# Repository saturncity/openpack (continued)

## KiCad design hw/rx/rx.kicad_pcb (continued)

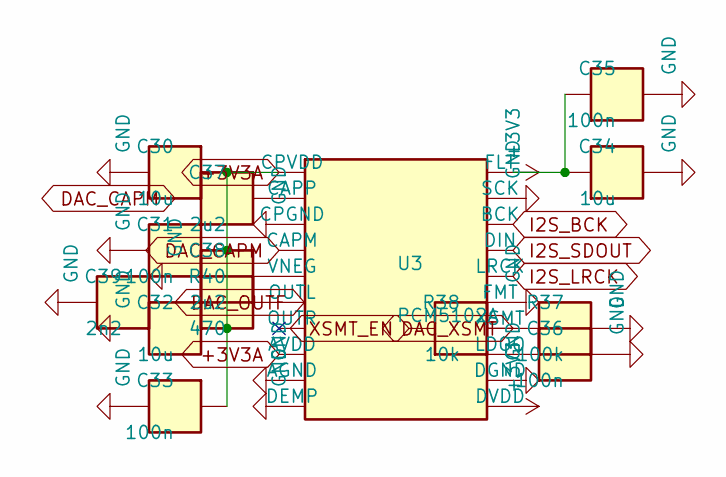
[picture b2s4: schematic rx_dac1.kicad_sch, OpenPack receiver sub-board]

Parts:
C30, C32, C34: 10u; C_0603_1608Metric; MPN C_10u_0603_X5R
C31, C33, C35, C36: 100n; C_0402_1005Metric; MPN C_100n_0402
C37, C38: 2u2; C_0603_1608Metric; MPN C_2u2_0603_X7R
C39: 2n2; C_0402_1005Metric; MPN C_2n2_0402_C0G
R37: 100k; R_0402_1005Metric; MPN R_0402_1%
R38: 10k; R_0402_1005Metric; MPN R_0402_1%
R40: 470; R_0402_1005Metric; MPN R_0402_1%
U3: PCM5102A; TSSOP-20_4.4x6.5mm_P0.65mm; MPN PCM5102APWR

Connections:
+3V3A: C30.1, C31.1, C32.1, C33.1, U3.1 (CPVDD), U3.8 (AVDD); also elsewhere on the board
DAC_CAPM: C37.2, U3.4 (CAPM)
DAC_CAPP: C37.1, U3.2 (CAPP)
DAC_LDOO: C36.1, U3.18 (LDOO)
DAC_OUTF: C39.1, R40.2; also elsewhere on the board
DAC_OUTL: R40.1, U3.6 (OUTL)
DAC_VNEG: C38.1, U3.5 (VNEG)
DAC_XSMT: R37.1, R38.2, U3.17 (XSMT); also elsewhere on the board
I2S_BCK: U3.13 (BCK); also elsewhere on the board
I2S_LRCK: U3.15 (LRCK); also elsewhere on the board
I2S_SDOUT: U3.14 (DIN); also elsewhere on the board
XSMT_EN: R38.1; also elsewhere on the board

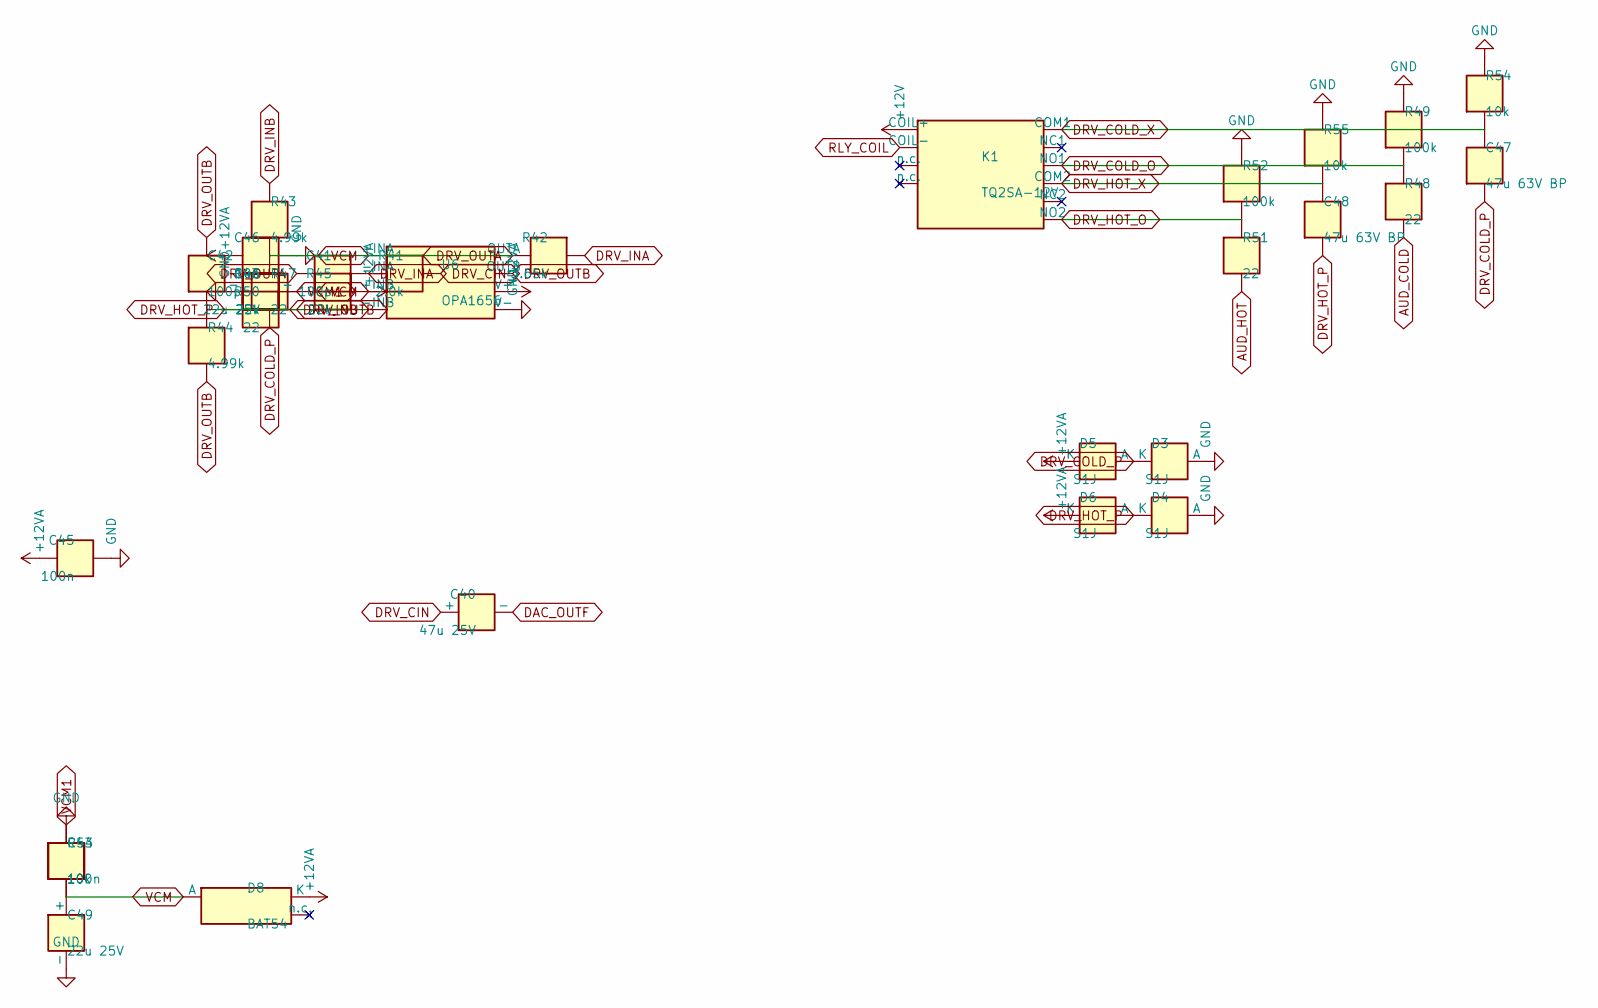
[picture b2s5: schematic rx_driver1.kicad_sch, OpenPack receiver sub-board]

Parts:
C40: 47u 25V; CP_Elec_5x5.4; MPN ALU_47u_25V
C41, C42: 100p; C_0402_1005Metric; MPN C_100p_0402_C0G
C43, C49: 22u 25V; CP_Elec_5x5.4; MPN ALU_22u_25V
C44, C45: 100n; C_0402_1005Metric; MPN C_100n_0402
C46: 10u; C_1206_3216Metric; MPN C_10u_1206_25V_X7R
C47, C48: 47u 63V BP; CP_Radial_D10.0mm_P5.00mm; MPN ALU_BP_47u_63V
D3, D4, D5, D6: S1J; D_SMA; MPN S1J
D8: BAT54; SOT-23; MPN BAT54,215
K1: TQ2SA-12V; Panasonic_TQ2SA; MPN TQ2SA-12V
R41: 2.0k; R_0402_1005Metric; MPN R_0402_1%
R42: 3.65k; R_0402_1005Metric; MPN R_0402_1%
R43, R44: 4.99k; R_0402_1005Metric; MPN R_0402_1%
R45, R46: 22k; R_0402_1005Metric; MPN R_0402_1%
R47, R48, R50, R51: 22; R_0603_1608Metric; MPN R_0603_1%
R49, R52: 100k; R_0402_1005Metric; MPN R_0402_1%
R53, R54, R55: 10k; R_0402_1005Metric; MPN R_0402_1%
U6: OPA1656; SOIC-8_3.9x4.9mm_P1.27mm; MPN OPA1656IDR

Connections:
AUD_COLD: R48.2; also elsewhere on the board
AUD_HOT: R51.2; also elsewhere on the board
DAC_OUTF: C40.2 (-); also elsewhere on the board
DRV_CIN: C40.1 (+), R41.1
DRV_COLD_O: K1.4 (NO1), R48.1, R49.1
DRV_COLD_P: C47.1, D3.1 (K), D5.2 (A), R47.2
DRV_COLD_X: C47.2, K1.3 (COM1), R54.1
DRV_HOT_O: K1.7 (NO2), R51.1, R52.1
DRV_HOT_X: C48.2, K1.8 (COM2), R55.1
DRV_INA: C41.1, R41.2, R42.1, U6.2 (-INA)
RLY_COIL: K1.10 (COIL-); also elsewhere on the board

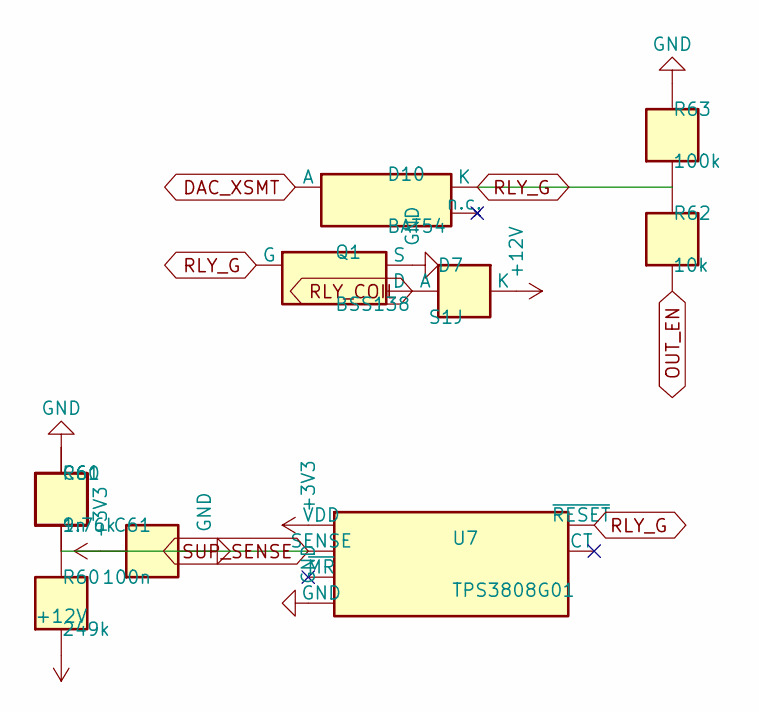
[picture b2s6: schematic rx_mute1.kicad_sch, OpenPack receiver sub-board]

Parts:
C60: 1n; C_0402_1005Metric; MPN C_1n_0402
C61: 100n; C_0402_1005Metric; MPN C_100n_0402
D7: S1J; D_SMA; MPN S1J
D10: BAT54; SOT-23; MPN BAT54,215
Q1: BSS138; SOT-23; MPN BSS138
R60: 249k; R_0402_1005Metric; MPN R_0402_1%
R61: 9.76k; R_0402_1005Metric; MPN R_0402_1%
R62: 10k; R_0402_1005Metric; MPN R_0402_1%
R63: 100k; R_0402_1005Metric; MPN R_0402_1%
U7: TPS3808G01; SOT-23-6; MPN TPS3808G01DBVR

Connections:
DAC_XSMT: D10.1 (A); also elsewhere on the board
OUT_EN: R62.1; also elsewhere on the board
RLY_COIL: D7.2 (A), Q1.3 (D); also elsewhere on the board
RLY_G: D10.3 (K), Q1.1 (G), R62.2, R63.1, U7.1 (~RESET); also elsewhere on the board

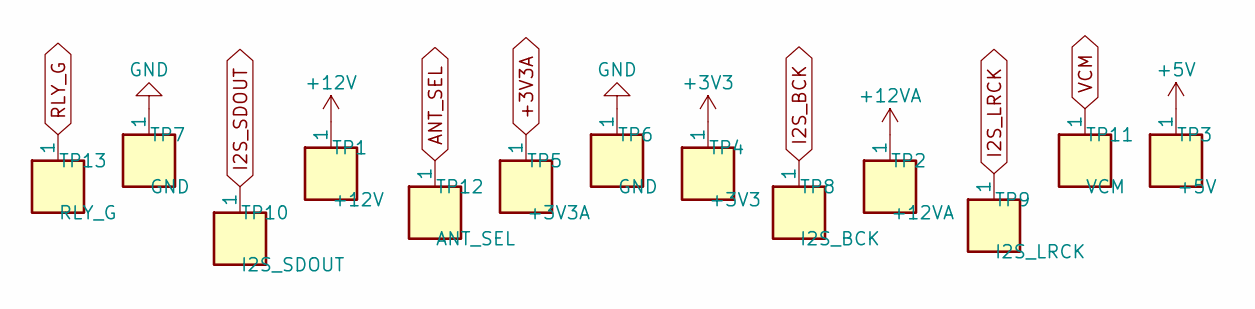
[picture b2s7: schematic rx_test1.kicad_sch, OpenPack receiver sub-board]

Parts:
TP1: +12V; TestPoint_Pad_D1.0mm; MPN TP-pad
TP2: +12VA; TestPoint_Pad_D1.0mm; MPN TP-pad
TP3: +5V; TestPoint_Pad_D1.0mm; MPN TP-pad
TP4: +3V3; TestPoint_Pad_D1.0mm; MPN TP-pad
TP5: +3V3A; TestPoint_Pad_D1.0mm; MPN TP-pad
TP6, TP7: GND; TestPoint_Pad_D1.0mm; MPN TP-pad
TP8: I2S_BCK; TestPoint_Pad_D1.0mm; MPN TP-pad
TP9: I2S_LRCK; TestPoint_Pad_D1.0mm; MPN TP-pad
TP10: I2S_SDOUT; TestPoint_Pad_D1.0mm; MPN TP-pad
TP11: VCM; TestPoint_Pad_D1.0mm; MPN TP-pad
TP12: ANT_SEL; TestPoint_Pad_D1.0mm; MPN TP-pad
TP13: RLY_G; TestPoint_Pad_D1.0mm; MPN TP-pad

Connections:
+3V3A: TP5.1; also elsewhere on the board
ANT_SEL: TP12.1; also elsewhere on the board
I2S_BCK: TP8.1; also elsewhere on the board
I2S_LRCK: TP9.1; also elsewhere on the board
I2S_SDOUT: TP10.1; also elsewhere on the board
RLY_G: TP13.1; also elsewhere on the board

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
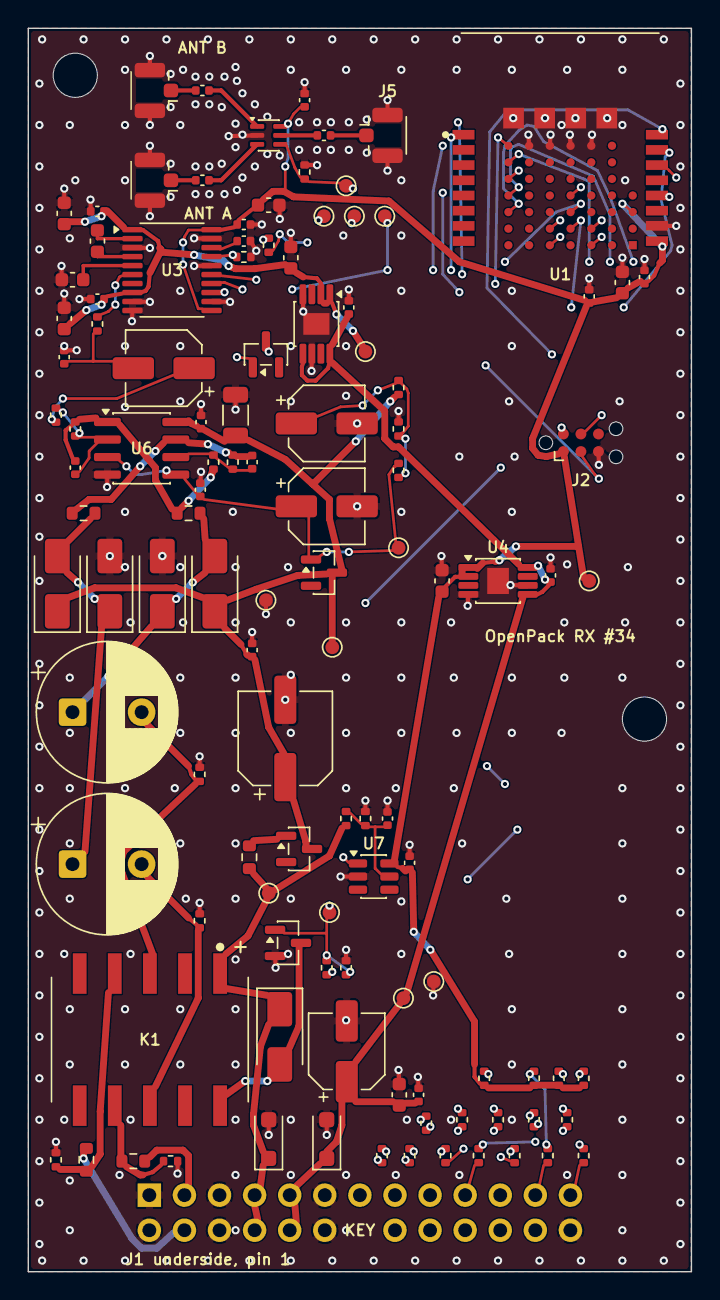
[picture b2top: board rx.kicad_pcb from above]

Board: 4 copper layers, 48.0 x 90.0 mm, 117 parts (1 on the bottom side), 67 nets.

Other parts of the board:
H1, H2: MountingHole_3.2mm_M3

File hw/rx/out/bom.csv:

refs,qty,value,mpn,unit_usd,ext_usd,unit_gbp,ext_gbp,uk_distributor,source
C1 C4 C6 C10 C30 C32 C34,7,10u,C_10u_0603_X5R,0.06,0.42,0.05,0.32,LCSC,est. (10 uF 10 V 0603 X5R)
C2 C8 C11 C12 C23 C31 C33 C35 C36 C44 C45 C61,12,100n,C_100n_0402,0.02,0.24,0.02,0.18,LCSC,est.
C3 C5,2,1u,C_1u_0402,0.03,0.06,0.02,0.05,LCSC,est.
C7,1,100u 25V,ALU_100u_25V,0.10,0.10,0.08,0.08,LCSC,"est. (100 uF 25 V SMD aluminium, 6.3 mm)"
C9 C40,2,47u 25V,ALU_47u_25V,0.08,0.16,0.06,0.12,LCSC,"est. (47 uF 25 V SMD aluminium, 5 mm)"
C20 C21 C22,3,10p,C_10p_0402_C0G,0.02,0.06,0.02,0.05,LCSC,est.
C37 C38,2,2u2,C_2u2_0603_X7R,0.03,0.06,0.02,0.05,LCSC,est.
C39,1,2n2,C_2n2_0402_C0G,0.02,0.02,0.02,0.02,LCSC,est.
C41 C42,2,100p,C_100p_0402_C0G,0.02,0.04,0.02,0.03,LCSC,est.
C43 C49,2,22u 25V,ALU_22u_25V,0.07,0.14,0.05,0.11,LCSC,"est. (22 uF 25 V SMD aluminium, 5 mm)"
C46,1,10u,C_10u_1206_25V_X7R,0.12,0.12,0.09,0.09,LCSC,est. (10 uF 25 V 1206 X7R)
C47 C48,2,47u 63V BP,ALU_BP_47u_63V,0.25,0.50,0.19,0.38,Farnell UK / RS UK,"est. (47 uF 63 V bipolar aluminium, 10 mm, e.g. Nichicon UEP series)"
C60,1,1n,C_1n_0402,0.02,0.02,0.02,0.02,LCSC,est.
D1,1,SMF15A,SMF15A,0.10,0.10,0.08,0.08,LCSC / Farnell UK,"est. (SMF 200 W TVS SOD-123F, q100)"
D2,1,SMF5.0A,SMF5.0A,0.10,0.10,0.08,0.08,LCSC / Farnell UK,"est. (SMF 200 W TVS SOD-123F, q100)"
D3 D4 D5 D6 D7,5,S1J,S1J,0.04,0.20,0.03,0.15,LCSC / Farnell UK,"est. (S1J 1 A 600 V SMA, IFSM 30 A, q100)"
D8 D9 D10,3,BAT54,"BAT54,215",0.03,0.09,0.02,0.07,LCSC / Farnell UK,"est. (Nexperia BAT54 SOT-23, q100)"
J1,1,backplane 2x13,PZ254V-12-26P,0.40,0.40,0.30,0.30,LCSC,"est. (XFCN 2x13 2.54 mm THT header, LCSC C22465887, 2401 in stock at JLC 2026-11-01; pin 14 cut for the key; mates the Harwin M20-7831346 socket + M20-003 key in position 14 on the main board, ADR-0018)"
J2,1,SWD,TC2030-pads,0.00,0.00,0.00,0.00,-,footprint only
J3,1,ANT_A,U.FL-R-SMT-1(10),0.45,0.45,0.34,0.34,Farnell UK / RS UK,"est. (Hirose U.FL receptacle, q100)"
J4,1,ANT_B,U.FL-R-SMT-1(10),0.45,0.45,0.34,0.34,Farnell UK / RS UK,"est. (Hirose U.FL receptacle, q100)"
J5,1,TO_MODULE,U.FL-R-SMT-1(10),0.45,0.45,0.34,0.34,Farnell UK / RS UK,"est. (Hirose U.FL receptacle, q100)"
K1,1,TQ2SA-12V,TQ2SA-12V,3.20,3.20,2.43,2.43,Farnell UK / RS UK,"est. (Panasonic TQ2 DPDT 12 V signal relay, q100; Farnell UK 1124056)"
Q1,1,BSS138,BSS138,0.05,0.05,0.04,0.04,LCSC / Farnell UK,"est. (onsemi BSS138 SOT-23, q100)"
R1,1,10,R_0603_1%,0.02,0.02,0.02,0.02,LCSC,est.
R20 R31 R32,3,100,R_0402_1%,0.02,0.06,0.02,0.05,LCSC,est.
R21 R22 R23 R25 R26 R27,6,1k,R_0402_1%,0.02,0.12,0.02,0.09,LCSC,est.
R24 R28 R29 R30 R38 R53 R54 R55 R62,9,10k,R_0402_1%,0.02,0.18,0.02,0.14,LCSC,est.
R33 R34 R35,3,DNP (100),DNP,0.00,0.00,0.00,0.00,-,not fitted (#81 review S4): pads only; fit 100 R 0402 for a digital add-on
R36 R37 R49 R52 R63,5,100k,R_0402_1%,0.02,0.10,0.02,0.08,LCSC,est.
R40,1,470,R_0402_1%,0.02,0.02,0.02,0.02,LCSC,est.
R41,1,2.0k,R_0402_1%,0.02,0.02,0.02,0.02,LCSC,est.
R42,1,3.65k,R_0402_1%,0.02,0.02,0.02,0.02,LCSC,est.
R43 R44,2,4.99k,R_0402_1%,0.02,0.04,0.02,0.03,LCSC,est.
R45 R46,2,22k,R_0402_1%,0.02,0.04,0.02,0.03,LCSC,est.
R47 R48 R50 R51,4,22,R_0603_1%,0.02,0.08,0.02,0.06,LCSC,est.
R60,1,249k,R_0402_1%,0.02,0.02,0.02,0.02,LCSC,est.
R61,1,9.76k,R_0402_1%,0.02,0.02,0.02,0.02,LCSC,est.
TP1,1,+12V,TP-pad,0.00,0.00,0.00,0.00,-,footprint only
TP2,1,+12VA,TP-pad,0.00,0.00,0.00,0.00,-,footprint only
TP3,1,+5V,TP-pad,0.00,0.00,0.00,0.00,-,footprint only
TP4,1,+3V3,TP-pad,0.00,0.00,0.00,0.00,-,footprint only
TP5,1,+3V3A,TP-pad,0.00,0.00,0.00,0.00,-,footprint only
TP6 TP7,2,GND,TP-pad,0.00,0.00,0.00,0.00,-,footprint only
TP8,1,I2S_BCK,TP-pad,0.00,0.00,0.00,0.00,-,footprint only
TP9,1,I2S_LRCK,TP-pad,0.00,0.00,0.00,0.00,-,footprint only
TP10,1,I2S_SDOUT,TP-pad,0.00,0.00,0.00,0.00,-,footprint only
TP11,1,VCM,TP-pad,0.00,0.00,0.00,0.00,-,footprint only
TP12,1,ANT_SEL,TP-pad,0.00,0.00,0.00,0.00,-,footprint only
TP13,1,RLY_G,TP-pad,0.00,0.00,0.00,0.00,-,footprint only
U1,1,BT40E,BT40E,12.86,12.86,9.77,9.77,DigiKey UK,"Digi-Key UK qty-100 cut tape GBP 9.7765, part 13174285, 803 in stock, 10 wk lead (read 2026-11-01)"
U2,1,PE4259,PE4259-63,0.41,0.41,0.31,0.31,LCSC C470892,"LCSC C470892 qty-100, via findchips.com/LCSC snapshot read 2026-10-31 (range $0.32-0.49)"
U3,1,PCM5102A,PCM5102APWR,2.80,2.80,2.13,2.13,Mouser UK / Farnell UK,"Digi-Key qty-100, via findchips.com snapshot read 2026-10-31 (Mouser q100 $2.78)"
U4 U5,2,TLV76733,TLV76733DGNR,0.40,0.80,0.30,0.61,Farnell UK / DigiKey UK / Mouser UK,"est. (TI TLV767 1 A 16 V LDO, HVSSOP-8, q100)"
U6,1,OPA1656,OPA1656IDR,1.84,1.84,1.40,1.40,DigiKey UK / Mouser UK,"Digi-Key qty-100 cut tape, 2026-10-31 (same as hw/pack/prices.py)"
U7,1,TPS3808G01,TPS3808G01DBVR,0.80,0.80,0.61,0.61,Farnell UK / Mouser UK,"est. (TI TPS3808 adjustable supervisor, SOT-23-6, q100)"
-,1,PCB 4-layer 48x90 mm (50 ohm RF traces),-,1.50,1.50,1.14,1.14,JLCPCB (ships to UK),est. (qty-100 panel share; size from the #34 layout)
-,1,U.FL-U.FL jumper 50 mm (switch out -> module u.FL),-,1.50,1.50,1.14,1.14,LCSC / RS UK,est.

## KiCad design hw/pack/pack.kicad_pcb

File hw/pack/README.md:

# hw/pack

The body-pack board is captured in SKiDL (`pack.py`). Decisions: ADR-0006 (front end), ADR-0007 (module), ADR-0012 (pinouts, bias filter, pad map).

- `python hw/pack/pack.py` (repo venv with `skidl` and `schematizer`) runs ERC, then writes `out/pack.net` (KiCad netlist), `out/bom.csv` (read by `audit.py` for PK-12), `out/sch/*.kicad_sch` (KiCad 9, one sheet per block) and `out/svg/*.svg` (previews). `--no-sch` skips the slow schematic render.
- `symbols.py` writes `openpack.kicad_sym`, box symbols built from datasheet pin tables. `prices.py` holds qty-100 prices, each with its source.
- Checks: `tests/test_pack_sch.py` (ERC clean, BOM current, key nets) and `tests/test_spice_preamp.py` (the same front end in ngspice).
- Layout (#34): `python3 hw/pack/layout.py`, run with the system python that has KiCad 10's `pcbnew`. It turns `out/pack.net` into `pack.kicad_pcb`: placement, a grid maze router (`router.py`), GND pours, DRC against `pack.kicad_dru` (JLCPCB rules), `outputs.py` (gerbers/drill/BOM/CPL/STEP in `out/fab`, PNG renders in `out/render`) and `fit.py` (enclosure fit). `footprints.py` generates `openpack.pretty` (BT40NE from the Fanstel drawing; the jack and holder footprints are provisional). Review and open items: `hw/REVIEW.md`. Checks: `tests/test_pack_layout.py`, `tests/mech/test_pack_fit.py`.

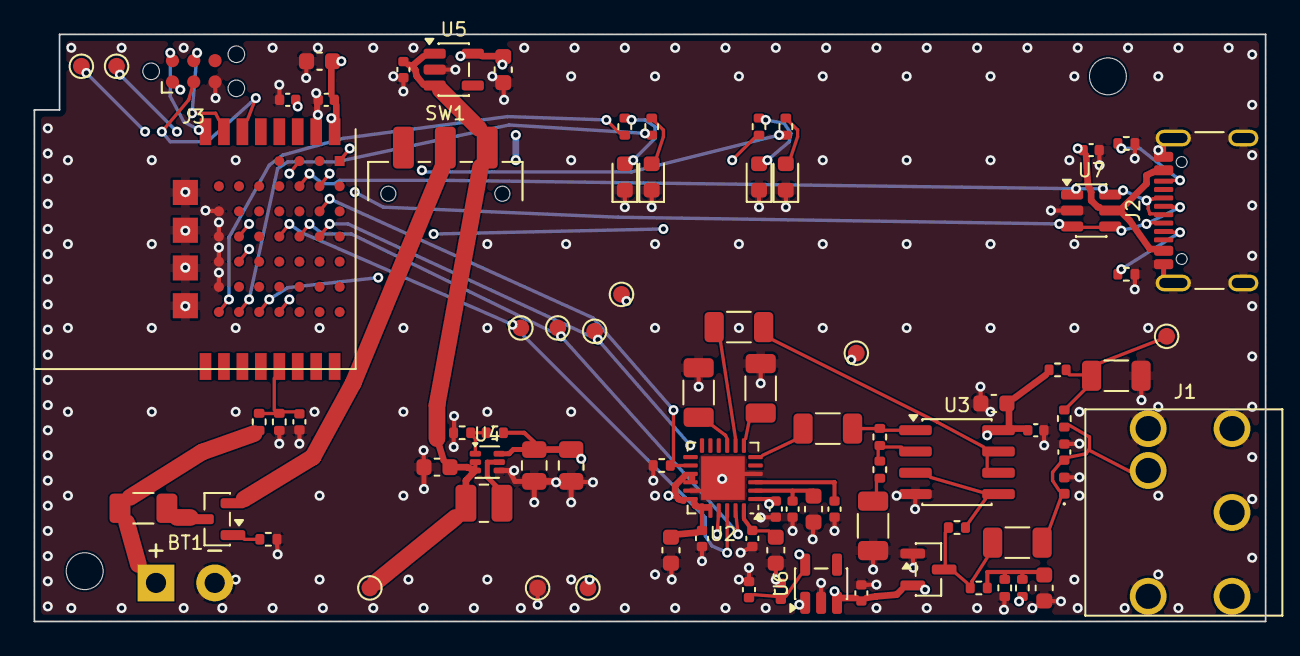
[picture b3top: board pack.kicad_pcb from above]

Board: 4 copper layers, 73.4 x 35.0 mm, 86 parts (0 on the bottom side), 50 nets.

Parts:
BT1: 18650 cradle contacts; Cell_Wire_Pads
C1, C5, C11, C14, C21, C24, C26, C28: 10u; C_0603_1608Metric
C2, C3: 22u; C_0805_2012Metric
C4, C6, C7, C19, C23, C31: 1u; C_0402_1005Metric
C8: 47u; C_1206_3216Metric
C9: 22p; C_0402_1005Metric
C10, C15, C16, C17, C18: 10u; C_1206_3216Metric
C12: 100u; C_1206_3216Metric
C13, C20, C22, C25, C27, C29, C30, C32: 100n; C_0402_1005Metric
D1: green BAT; LED_0603_1608Metric
D2: red BAT LOW; LED_0603_1608Metric
D3: amber PEAK; LED_0603_1608Metric
D4: red CLIP; LED_0603_1608Metric
D5: TPD1E10B06; D_0402_1005Metric
D6: BAV199; SOT-23
F1: 3A fast; Fuse_1206_3216Metric
H1, H2: MountingHole_2.2mm_M2
J1: 3.5mm locking; SameSky_SJ1-3543
J2: USB-C; USB_C_Receptacle_GCT_USB4105-xx-A_16P_TopMnt_Horizontal
J3: SWD; Tag-Connect_TC2030-IDC-NL_2x03_P1.27mm_Vertical
L1: 1uH 4.7A; L_1008_2520Metric
Q1: DMG2305UX; SOT-23
R1, R3, R6, R8, R11: 100k; R_0402_1005Metric
R2: 732k; R_0402_1005Metric
R4, R20: 100; R_0402_1005Metric
R5: 2.2k; R_0402_1005Metric
R7: 180k; R_0402_1005Metric
R9, R10: 330; R_0402_1005Metric
R12, R13: 1M; R_0402_1005Metric
R14, R15, R16, R17: 1k; R_0402_1005Metric
R18, R19: 5.1k; R_0402_1005Metric
SW1: recessed slide; SW_SPDT_CK_JS102011SAQN
TP1: UART_TX; TestPoint_Pad_D1.0mm
TP2: UART_RX; TestPoint_Pad_D1.0mm
TP3: VSYS; TestPoint_Pad_D1.0mm
TP4: +5V; TestPoint_Pad_D1.0mm
TP5: +3V3; TestPoint_Pad_D1.0mm
TP6: +3V3A; TestPoint_Pad_D1.0mm
TP7: +5V_BIAS; TestPoint_Pad_D1.0mm
TP8: GND; TestPoint_Pad_D1.0mm
TP9: I2S_BCLK; TestPoint_Pad_D1.0mm
TP10: I2S_FSYNC; TestPoint_Pad_D1.0mm
TP11: I2S_SDOUT; TestPoint_Pad_D1.0mm
U1: BT40NE; Fanstel_BT40NE
U2: PCM1840; WQFN-24-1EP_4x4mm_P0.5mm_EP2.6x2.6mm
U3: OPA1656; SOIC-8_3.9x4.9mm_P1.27mm
U4: TPS61023; SOT-563
U5, U6: TLV75533P; SOT-23-5
U7: USBLC6-2SC6; SOT-23-6

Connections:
+3V3: C5.1, C26.1, C27.1, C28.1, C29.1, C32.1, J3.1, TP5.1, U1.9, U1.F4, U2.15, U2.16, U2.18, U2.19, U2.20, U5.5
+3V3A: C7.1, C19.1, C20.1, TP6.1, U2.1, U6.5
+5V: C2.1, C3.1, C6.1, C13.1, C14.1, D6.2, R2.1, R4.1, R7.1, TP4.1, U3.8, U4.6, U6.1, U6.3
+5V_BIAS: C8.1, R4.2, R5.1, TP7.1
ADC_AREG: C21.1, C22.1, U2.2
ADC_DREG: C24.1, C25.1, U2.24
ADC_IN1M: C16.1, U2.7
ADC_IN1P: C15.2, U2.6
ADC_IN2M: C18.1, U2.9
ADC_IN2P: C17.2, U2.8
ADC_SHDNZ: R11.1, U1.D5, U2.14
ADC_VREF: C23.1, U2.3
BAT+: BT1.1, F1.1, R12.1
BAT_F: F1.2, Q1.3
BOOST_FB: R2.2, R3.1, U4.1
BOOST_SW: L1.2, U4.5
GND: BT1.2, C1.2, C2.2, C3.2, C4.2, C5.2, C6.2, C7.2, C8.2, C9.2, C11.2, C12.2, C13.2, C14.2, C16.2, C18.2, C19.2, C20.2, C21.2, C22.2, C23.2, C24.2, C25.2, C26.2, C27.2, C28.2, C29.2, C30.2, C31.2, C32.2, D1.1, D2.1, D3.1, D4.1, D5.2, D6.1, J1.MP, J1.R, J1.S, J2.A1, J2.A12, J2.B1, J2.B12, J2.SH, J3.5, R1.2, R3.2, R8.2, R11.2, R13.2, R18.2, R19.2, TP8.1, U1.10, U1.A0, U1.B0, U1.C0, U1.D0, U1.H0, U1.H1, U1.H2, U1.H3, U2.4, U2.17, U2.25, U3.4, U4.4, U5.2, U6.2, U7.2
I2S_BCLK: TP9.1, U1.C3, U2.22
I2S_FSYNC: TP10.1, U1.C4, U2.23
I2S_SDOUT: TP11.1, U1.C5, U2.21
LED_BAT_LOW: R15.1, U1.Z1
LED_BAT_LOW_A: D2.2, R15.2
LED_BAT_OK: R14.1, U1.Z0
LED_BAT_OK_A: D1.2, R14.2
LED_CLIP: R17.1, U1.Z3
LED_CLIP_A: D4.2, R17.2
LED_PEAK: R16.1, U1.Z2
LED_PEAK_A: D3.2, R16.2
MIC: C9.1, C10.1, D5.1, J1.T, R5.2
PRE_CG: C12.1, R10.2
PRE_INM: R9.2, R10.1, U3.2
PRE_INP: R20.2, U3.3, U3.5
PRE_NP: C10.2, D6.3, R6.1, R20.1
PRE_OUTA: C15.1, R9.1, U3.1
PRE_OUTB: C17.1, U3.6, U3.7
Q1_G: Q1.1, R1.1
SWDCLK: J3.4, U1.15
SWDIO: J3.2, U1.16
UART_RX: TP2.1, U1.C1
UART_TX: TP1.1, U1.B1
USB_CC1: J2.A5, R18.1
USB_CC2: J2.B5, R19.1
USB_D+: J2.A6, J2.B6, U1.E4, U7.1, U7.6
USB_D-: J2.A7, J2.B7, U1.E5, U7.3, U7.4
USB_VBUS: C31.1, J2.A4, J2.A9, J2.B4, J2.B9, U1.F6, U7.5
VBAT_RP: Q1.2, SW1.2
VBAT_SENSE: C30.1, R12.2, R13.1, U1.5
VCM: C11.1, R6.2, R7.2, R8.1
VSYS: C1.1, C4.1, L1.1, SW1.3, TP3.1, U4.2, U4.3, U5.1, U5.3
nRESET: J3.3, U1.14

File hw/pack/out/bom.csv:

refs,qty,value,mpn,unit_usd,ext_usd,source
BT1,1,18650 cradle contacts,MY-18650-04-J/05-J,0.2265,0.23,"LCSC C19184125 MY-18650-04-J (+ plate) $0.1181 @50-149 + C19184124 MY-18650-05-J (- spring) $0.1084 (only ladder shown, @5); read 2026-11-01"
C1 C5 C11 C14 C21 C24 C26 C28,8,10u,C_10u_0603_X5R,0.0600,0.48,est. (10 uF 10 V 0603 X5R)
C10 C15 C16 C17 C18,5,10u,C_10u_1206_X7R,0.1200,0.60,est. (10 uF 16 V 1206 X7R)
C12,1,100u,GRM31CR60J107ME39L,0.3500,0.35,est. (100 uF 6.3 V 1206)
C13 C20 C22 C25 C27 C29 C30 C32,8,100n,C_100n_0402,0.0013,0.01,"LCSC C1525 (Samsung CL05B104KO5NNNC, 100 nF 16 V X7R 0402), qty 100, 2026-10-31"
C4 C6 C7 C19 C23 C31,6,1u,C_1u_0402,0.0300,0.18,est.
C2 C3,2,22u,GRM21BR61A226ME51L,0.1200,0.24,est. (22 uF 10 V 0805)
C8,1,47u,GRM31CR61A476ME15L,0.2500,0.25,est. (47 uF 10 V 1206)
C9,1,22p,C_22p_0402_C0G,0.0200,0.02,est.
D1,1,green BAT,LTST-C191KGKT,0.1500,0.15,"Digi-Key listing price (q1 assumed); AlInGaP green, Vf ~2.0 V"
D2,1,red BAT LOW,LTST-C191KRKT,0.1500,0.15,est. = KGKT price (same Lite-On series)
D3,1,amber PEAK,LTST-C191KSKT,0.1500,0.15,est. = KGKT price (same Lite-On series)
D4,1,red CLIP,LTST-C191KRKT,0.1500,0.15,est. = KGKT price (same Lite-On series)
D5,1,TPD1E10B06,TPD1E10B06DPYR,0.4100,0.41,Digi-Key listing price (tier not shown; q1 assumed)
D6,1,BAV199,"BAV199,215",0.2100,0.21,Digi-Key listing price (tier not shown; q1 assumed)
F1,1,3A fast,SF-1206F300-2,0.5200,0.52,"Digi-Key qty-100 cut tape, 2026-10-31 (Bourns 3 A 1206 fast, 23 mOhm cold)"
J1,1,3.5mm locking,SJ1-3543,1.6100,1.61,"Digi-Key qty-100 cut tape, 2026-10-31 (Same Sky, M6 threaded bushing + nut); fallback Switchcraft 35RAPC3BH3 $3.29"
J2,1,USB-C,USB4105-GF-A,0.5700,0.57,"Digi-Key qty-100 cut tape, 2026-10-31"
J3,1,SWD,TC2030-pads,0.0000,0.00,footprint only
L1,1,1uH 4.7A,DFE252012F-1R0M=P2,0.1700,0.17,"Digi-Key qty-100 cut tape, 2026-10-31"
Q1,1,DMG2305UX,DMG2305UX-7,0.1000,0.10,est.
R1 R3 R6 R8 R11,5,100k,R_0402_1%,0.0064,0.03,"LCSC C407692 (and C11702, C25076, C25741, C26083, C25905), qty 100, 2026-10-31; highest of the six used for all"
R9 R10,2,330,R_0402_1%,0.0064,0.01,"LCSC C407692 (and C11702, C25076, C25741, C26083, C25905), qty 100, 2026-10-31; highest of the six used for all"
R12 R13,2,1M,R_0402_1%,0.0064,0.01,"LCSC C407692 (and C11702, C25076, C25741, C26083, C25905), qty 100, 2026-10-31; highest of the six used for all"
R14 R15 R16 R17,4,1k,R_0402_1%,0.0064,0.03,"LCSC C407692 (and C11702, C25076, C25741, C26083, C25905), qty 100, 2026-10-31; highest of the six used for all"
R18 R19,2,5.1k,R_0402_1%,0.0064,0.01,"LCSC C407692 (and C11702, C25076, C25741, C26083, C25905), qty 100, 2026-10-31; highest of the six used for all"
R2,1,732k,R_0402_1%,0.0064,0.01,"LCSC C407692 (and C11702, C25076, C25741, C26083, C25905), qty 100, 2026-10-31; highest of the six used for all"
R4 R20,2,100,R_0402_1%,0.0064,0.01,"LCSC C407692 (and C11702, C25076, C25741, C26083, C25905), qty 100, 2026-10-31; highest of the six used for all"
R5,1,2.2k,R_0402_1%,0.0064,0.01,"LCSC C407692 (and C11702, C25076, C25741, C26083, C25905), qty 100, 2026-10-31; highest of the six used for all"
R7,1,180k,R_0402_1%,0.0064,0.01,"LCSC C407692 (and C11702, C25076, C25741, C26083, C25905), qty 100, 2026-10-31; highest of the six used for all"
SW1,1,recessed slide,JS102011SAQN,0.6400,0.64,"Digi-Key qty-100 cut tape, 2026-10-31"
TP1,1,UART_TX,TP-pad,0.0000,0.00,footprint only
TP10,1,I2S_FSYNC,TP-pad,0.0000,0.00,footprint only
TP11,1,I2S_SDOUT,TP-pad,0.0000,0.00,footprint only
TP2,1,UART_RX,TP-pad,0.0000,0.00,footprint only
TP3,1,VSYS,TP-pad,0.0000,0.00,footprint only
TP4,1,+5V,TP-pad,0.0000,0.00,footprint only
TP5,1,+3V3,TP-pad,0.0000,0.00,footprint only
TP6,1,+3V3A,TP-pad,0.0000,0.00,footprint only
TP7,1,+5V_BIAS,TP-pad,0.0000,0.00,footprint only
TP8,1,GND,TP-pad,0.0000,0.00,footprint only
TP9,1,I2S_BCLK,TP-pad,0.0000,0.00,footprint only
U1,1,BT40NE,BT40NE,13.4700,13.47,"Fanstel direct, qty-100 break on fanstel.com/bt40f-nrf5340 (read 2026-10-31, #31 comment)"
U2,1,PCM1840,PCM1840IRTWR,3.3700,3.37,"Digi-Key qty-100 cut tape, 2026-10-31"
U3,1,OPA1656,OPA1656IDR,1.8400,1.84,"Digi-Key qty-100 cut tape, 2026-10-31"
U4,1,TPS61023,TPS61023DRLR,0.8000,0.80,"Digi-Key qty-100 cut tape, 2026-10-31"
U5 U6,2,TLV75533P,TLV75533PDBVR,0.2300,0.46,"Digi-Key qty-100 cut tape, 2026-10-31"
U7,1,USBLC6-2SC6,USBLC6-2SC6,0.2100,0.21,"Digi-Key qty-100 cut tape, 2026-10-31"
-,1,PCB 4-layer ~60x90 mm,-,2.5000,2.50,est. (audit.py v1 figure)
-,1,3D-printed PETG enclosure + clip (mech/),-,2.5000,2.50,est. (audit.py v1 figure)
-,1,"IPEX 1.13 pigtail BWIPX1-SMA-1.13L150 (BAT Wireless, SMA cut off)",-,0.6015,0.60,"LCSC C784404 $0.6015 @100, 1908 in stock, read 2026-11-01"
-,1,whip: 31 mm 0.9 mm tinned Cu wire + 20 mm heat-shrink,-,0.0300,0.03,est.
-,1,cell leads: 2 x 60 mm 24 AWG silicone wire,-,0.0200,0.02,est.
-,2,"M2 x 6 thread-forming pan screw (PT type, zinc)",-,0.1120,0.22,"Fastener Superstore 585907 M2-0.89x6 PT pan Phillips zinc, $559 per 5000 carton = $0.112 (read 2026-11-01; LCSC/Accu listing not found)"

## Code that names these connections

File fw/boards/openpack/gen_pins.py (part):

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            "I2S_SDOUT":  ("psel", "i2s0", "I2S_SDIN"),      # PCM1840 SDOUT -> nRF SDIN
            "UART_TX":    ("psel", "uart0", "UART_TX"),      # test pad TP1, console
            "UART_RX":    ("psel", "uart0", "UART_RX"),      # test pad TP2
            "ADC_SHDNZ":  ("user", "shdnz", "GPIO_ACTIVE_HIGH"),  # PCM1840 out of shutdown when high (R11 pull-down)
            "LED_BAT_OK": ("led", "led_bat_ok", "PK-8 green: battery OK"),
            "LED_BAT_LOW": ("led", "led_bat_low", "PK-8 red: battery low"),
            "LED_PEAK":   ("led", "led_peak", "PK-8 amber: peak >= -10 dBFS"),
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            "I2S_SDOUT": ("psel", "i2s0", "I2S_SDOUT"),
            "UART_TX":   ("psel", "uart0", "UART_TX"),       # backplane to host, console + protocol
            "UART_RX":   ("psel", "uart0", "UART_RX"),
            "XSMT_EN":   ("user", "xsmt", "GPIO_ACTIVE_HIGH"),    # PCM5102A soft un-mute (100k pull-down)
            "OUT_EN":    ("user", "out-en", "GPIO_ACTIVE_HIGH"),  # relay K1 closed when high (100k pull-down)
            "SLOT0":     ("user", "slot", "GPIO_ACTIVE_HIGH"),    # slot strap bits, 10k pull-ups: GND = 0
            "SLOT1":     ("user", "slot", "GPIO_ACTIVE_HIGH"),
            "SLOT2":     ("user", "slot", "GPIO_ACTIVE_HIGH"),
            "LED_LOCK":  ("led", "led_lock", "RK-4 front panel: lock"),
            "LED_PEAK":  ("led", "led_peak", "RK-4 front panel: peak"),
            "BOOT":      ("key", "boot_btn", "BOOT strap: MCUboot serial recovery (low at reset)"),
            "ANT_SEL":   ("fwd", "ant-sel", "GPIO_ACTIVE_HIGH"),  # PE4259 CTRL, net core; low = antenna A
        },
        "fem": {}, "fem_spi": (),
    },
}
IGNORE = {"GND", "+3V3", "SWDIO", "SWDCLK", "nRESET"}   # power, SWD, reset: not firmware pins
BAD_PINS = {(0, 0): "LFXO XL1", (0, 1): "LFXO XL2", (0, 2): "NFC1", (0, 3): "NFC2"}
USB_PADS = {"D+", "D-", "VBUS"}

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
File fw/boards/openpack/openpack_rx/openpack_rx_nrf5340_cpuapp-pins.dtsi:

/* GENERATED by fw/boards/openpack/gen_pins.py from hw/rx/out/rx.net (hw/rx/rx.py, ADR-0014). Do not edit:
 * change the schematic, rerun hw/rx/rx.py, then gen_pins.py.
 * openpack_rx/nrf5340/cpuapp. tests/test_fw_board_pins.py checks it against the netlist. */

&pinctrl {
	/* i2s0: I2S_LRCK_M=I2S_LRCK@C4, I2S_SCK_M=I2S_BCK@C3, I2S_SDOUT=I2S_SDOUT@B6 */
	i2s0_default: i2s0_default {
		group1 {
			psels = <NRF_PSEL(I2S_LRCK_M, 0, 23)>,
				<NRF_PSEL(I2S_SCK_M, 0, 24)>,
				<NRF_PSEL(I2S_SDOUT, 0, 13)>;
		};
	};
	i2s0_sleep: i2s0_sleep {
		group1 {
			psels = <NRF_PSEL(I2S_LRCK_M, 0, 23)>,
				<NRF_PSEL(I2S_SCK_M, 0, 24)>,
				<NRF_PSEL(I2S_SDOUT, 0, 13)>;
			low-power-enable;
		};
	};
	/* uart0: UART_RX=UART_RX@D5, UART_TX=UART_TX@C5 */
	uart0_default: uart0_default {
		group1 {
			psels = <NRF_PSEL(UART_TX, 0, 20)>;
		};
		group2 {
			psels = <NRF_PSEL(UART_RX, 0, 22)>;
			bias-pull-up;
		};
	};
	uart0_sleep: uart0_sleep {
		group1 {
			psels = <NRF_PSEL(UART_TX, 0, 20)>;
			low-power-enable;
		};
		group2 {
			psels = <NRF_PSEL(UART_RX, 0, 22)>;
			low-power-enable;
			bias-pull-up;
		};
	};
};

&i2s0 {
	pinctrl-0 = <&i2s0_default>;
	pinctrl-1 = <&i2s0_sleep>;
	pinctrl-names = "default", "sleep";
};

&uart0 {
	pinctrl-0 = <&uart0_default>;
	pinctrl-1 = <&uart0_sleep>;
	pinctrl-names = "default", "sleep";
};

/ {
	leds {
		compatible = "gpio-leds";
		led_lock: led_lock {
			gpios = <&gpio1 9 GPIO_ACTIVE_HIGH>; /* LED_LOCK@Z0 */
			label = "RK-4 front panel: lock";
		};
		led_peak: led_peak {
			gpios = <&gpio1 10 GPIO_ACTIVE_HIGH>; /* LED_PEAK@Z1 */
			label = "RK-4 front panel: peak";
		};
	};

	buttons {
		compatible = "gpio-keys";
		boot_btn: boot_btn {
			gpios = <&gpio1 2 GPIO_ACTIVE_LOW>; /* BOOT@1, external pull-up */
			label = "BOOT strap: MCUboot serial recovery (low at reset)";
			zephyr,code = <INPUT_KEY_0>;
		};
	};

	aliases {
		mcuboot-button0 = &boot_btn;
	};

	zephyr,user {
		out-en-gpios = <&gpio0 11 GPIO_ACTIVE_HIGH>; /* OUT_EN@12 */
		slot-gpios = <&gpio1 11 GPIO_ACTIVE_HIGH>, <&gpio1 12 GPIO_ACTIVE_HIGH>, <&gpio1 13 GPIO_ACTIVE_HIGH>; /* SLOT0@Z2, SLOT1@Z3, SLOT2@Z4 */
		xsmt-gpios = <&gpio0 12 GPIO_ACTIVE_HIGH>; /* XSMT_EN@B5 */
	};

	/* net-core pins, handed over at net-core boot (SOC_NRF_GPIO_FORWARDER_FOR_NRF5340) */
	gpio_fwd: nrf-gpio-forwarder {
		compatible = "nordic,nrf-gpio-forwarder";
		status = "okay";

		net {
			gpios = <&gpio1 1 0>;
			/* ANT_SEL@D6 */
		};
	};
};

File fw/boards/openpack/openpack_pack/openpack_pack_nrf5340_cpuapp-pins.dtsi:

/* GENERATED by fw/boards/openpack/gen_pins.py from hw/pack/out/pack.net (hw/pack/pack.py, ADR-0012). Do not edit:
 * change the schematic, rerun hw/pack/pack.py, then gen_pins.py.
 * openpack_pack/nrf5340/cpuapp. tests/test_fw_board_pins.py checks it against the netlist. */

&pinctrl {
	/* i2s0: I2S_LRCK_M=I2S_FSYNC@C4, I2S_SCK_M=I2S_BCLK@C3, I2S_SDIN=I2S_SDOUT@C5 */
	i2s0_default: i2s0_default {
		group1 {
			psels = <NRF_PSEL(I2S_LRCK_M, 0, 23)>,
				<NRF_PSEL(I2S_SCK_M, 0, 24)>,
				<NRF_PSEL(I2S_SDIN, 0, 20)>;
		};
	};
	i2s0_sleep: i2s0_sleep {
		group1 {
			psels = <NRF_PSEL(I2S_LRCK_M, 0, 23)>,
				<NRF_PSEL(I2S_SCK_M, 0, 24)>,
				<NRF_PSEL(I2S_SDIN, 0, 20)>;
			low-power-enable;
		};
	};
	/* uart0: UART_RX=UART_RX@C1, UART_TX=UART_TX@B1 */
	uart0_default: uart0_default {
		group1 {
			psels = <NRF_PSEL(UART_TX, 0, 19)>;
		};
		group2 {
			psels = <NRF_PSEL(UART_RX, 0, 31)>;
			bias-pull-up;
		};
	};
	uart0_sleep: uart0_sleep {
		group1 {
			psels = <NRF_PSEL(UART_TX, 0, 19)>;
			low-power-enable;
		};
		group2 {
			psels = <NRF_PSEL(UART_RX, 0, 31)>;
			low-power-enable;
			bias-pull-up;
		};
	};
};

&i2s0 {
	pinctrl-0 = <&i2s0_default>;
	pinctrl-1 = <&i2s0_sleep>;
	pinctrl-names = "default", "sleep";
};

&uart0 {
	pinctrl-0 = <&uart0_default>;
	pinctrl-1 = <&uart0_sleep>;
	pinctrl-names = "default", "sleep";
};

/ {
	leds {
		compatible = "gpio-leds";
		led_bat_low: led_bat_low {
			gpios = <&gpio1 10 GPIO_ACTIVE_HIGH>; /* LED_BAT_LOW@Z1 */
			label = "PK-8 red: battery low";
		};
		led_bat_ok: led_bat_ok {
			gpios = <&gpio1 9 GPIO_ACTIVE_HIGH>; /* LED_BAT_OK@Z0 */
			label = "PK-8 green: battery OK";
		};
		led_clip: led_clip {
			gpios = <&gpio1 12 GPIO_ACTIVE_HIGH>; /* LED_CLIP@Z3 */
			label = "PK-8 red: clip >= -7 dBFS";
		};
		led_peak: led_peak {
			gpios = <&gpio1 11 GPIO_ACTIVE_HIGH>; /* LED_PEAK@Z2 */
			label = "PK-8 amber: peak >= -10 dBFS";
		};
	};

	zephyr,user {
		shdnz-gpios = <&gpio0 22 GPIO_ACTIVE_HIGH>; /* ADC_SHDNZ@D5 */
	};

	vbat: vbat {
		compatible = "voltage-divider";
		io-channels = <&adc 0>;
		/* VBAT_SENSE@5 (P0.04/AIN0): R12 1M from BAT+, R13 1M to GND */
		output-ohms = <1000000>;
		full-ohms = <2000000>;
	};

	/* net-core pins, handed over at net-core boot (SOC_NRF_GPIO_FORWARDER_FOR_NRF5340) */
	gpio_fwd: nrf-gpio-forwarder {
		compatible = "nordic,nrf-gpio-forwarder";
		status = "okay";

		net {
			gpios = <&gpio0 21 0>,
				<&gpio0 27 0>,
				<&gpio0 26 0>,
				<&gpio1 4 0>,
				<&gpio1 5 0>;
			/* nRF21540 tx-en-gpios@C2, nRF21540 rx-en-gpios@D2, nRF21540 pdn-gpios@D1, nRF21540 mode-gpios@E0, nRF21540 ant-sel-gpios@E1 */
		};
	};
};

&adc {
	#address-cells = <1>;
	#size-cells = <0>;

	channel@0 {
		reg = <0>;
		zephyr,gain = "ADC_GAIN_1_6"; /* 3.6 V full scale vs. 2.1 V at 4.2 V cell */
		zephyr,reference = "ADC_REF_INTERNAL";
		zephyr,acquisition-time = <ADC_ACQ_TIME(ADC_ACQ_TIME_MICROSECONDS, 40)>; /* high-Z divider */
		zephyr,input-positive = <NRF_SAADC_AIN0>; /* VBAT_SENSE@5 P0.04/AIN0 */
		zephyr,resolution = <12>;
		zephyr,oversampling = <4>;
	};
};
